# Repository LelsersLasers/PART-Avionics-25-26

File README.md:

# PART Avionics 2025-2026

PART (Purdue Aerial Robotics Team). Work by Comp Avionics and R&D Avionics.

KiCad projects:
- [PDU (power distribution unit)](https://kicanvas.org/?github=https%3A%2F%2Fgithub.com%2FLelsersLasers%2FPART-Avionics-25-26%2Ftree%2Fmain%2FPDB)
- [Pixhawk Carrier](https://kicanvas.org/?github=https%3A%2F%2Fgithub.com%2FLelsersLasers%2FPART-Avionics-25-26%2Ftree%2Fmain%2FKiCad_Main_PCB)

Embedded code:
- PDU

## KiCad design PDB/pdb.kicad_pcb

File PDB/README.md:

# PART Avionics PDB
This is the git repository for the KiCAD schematic & PCB files for the new aircraft's power distribution board.

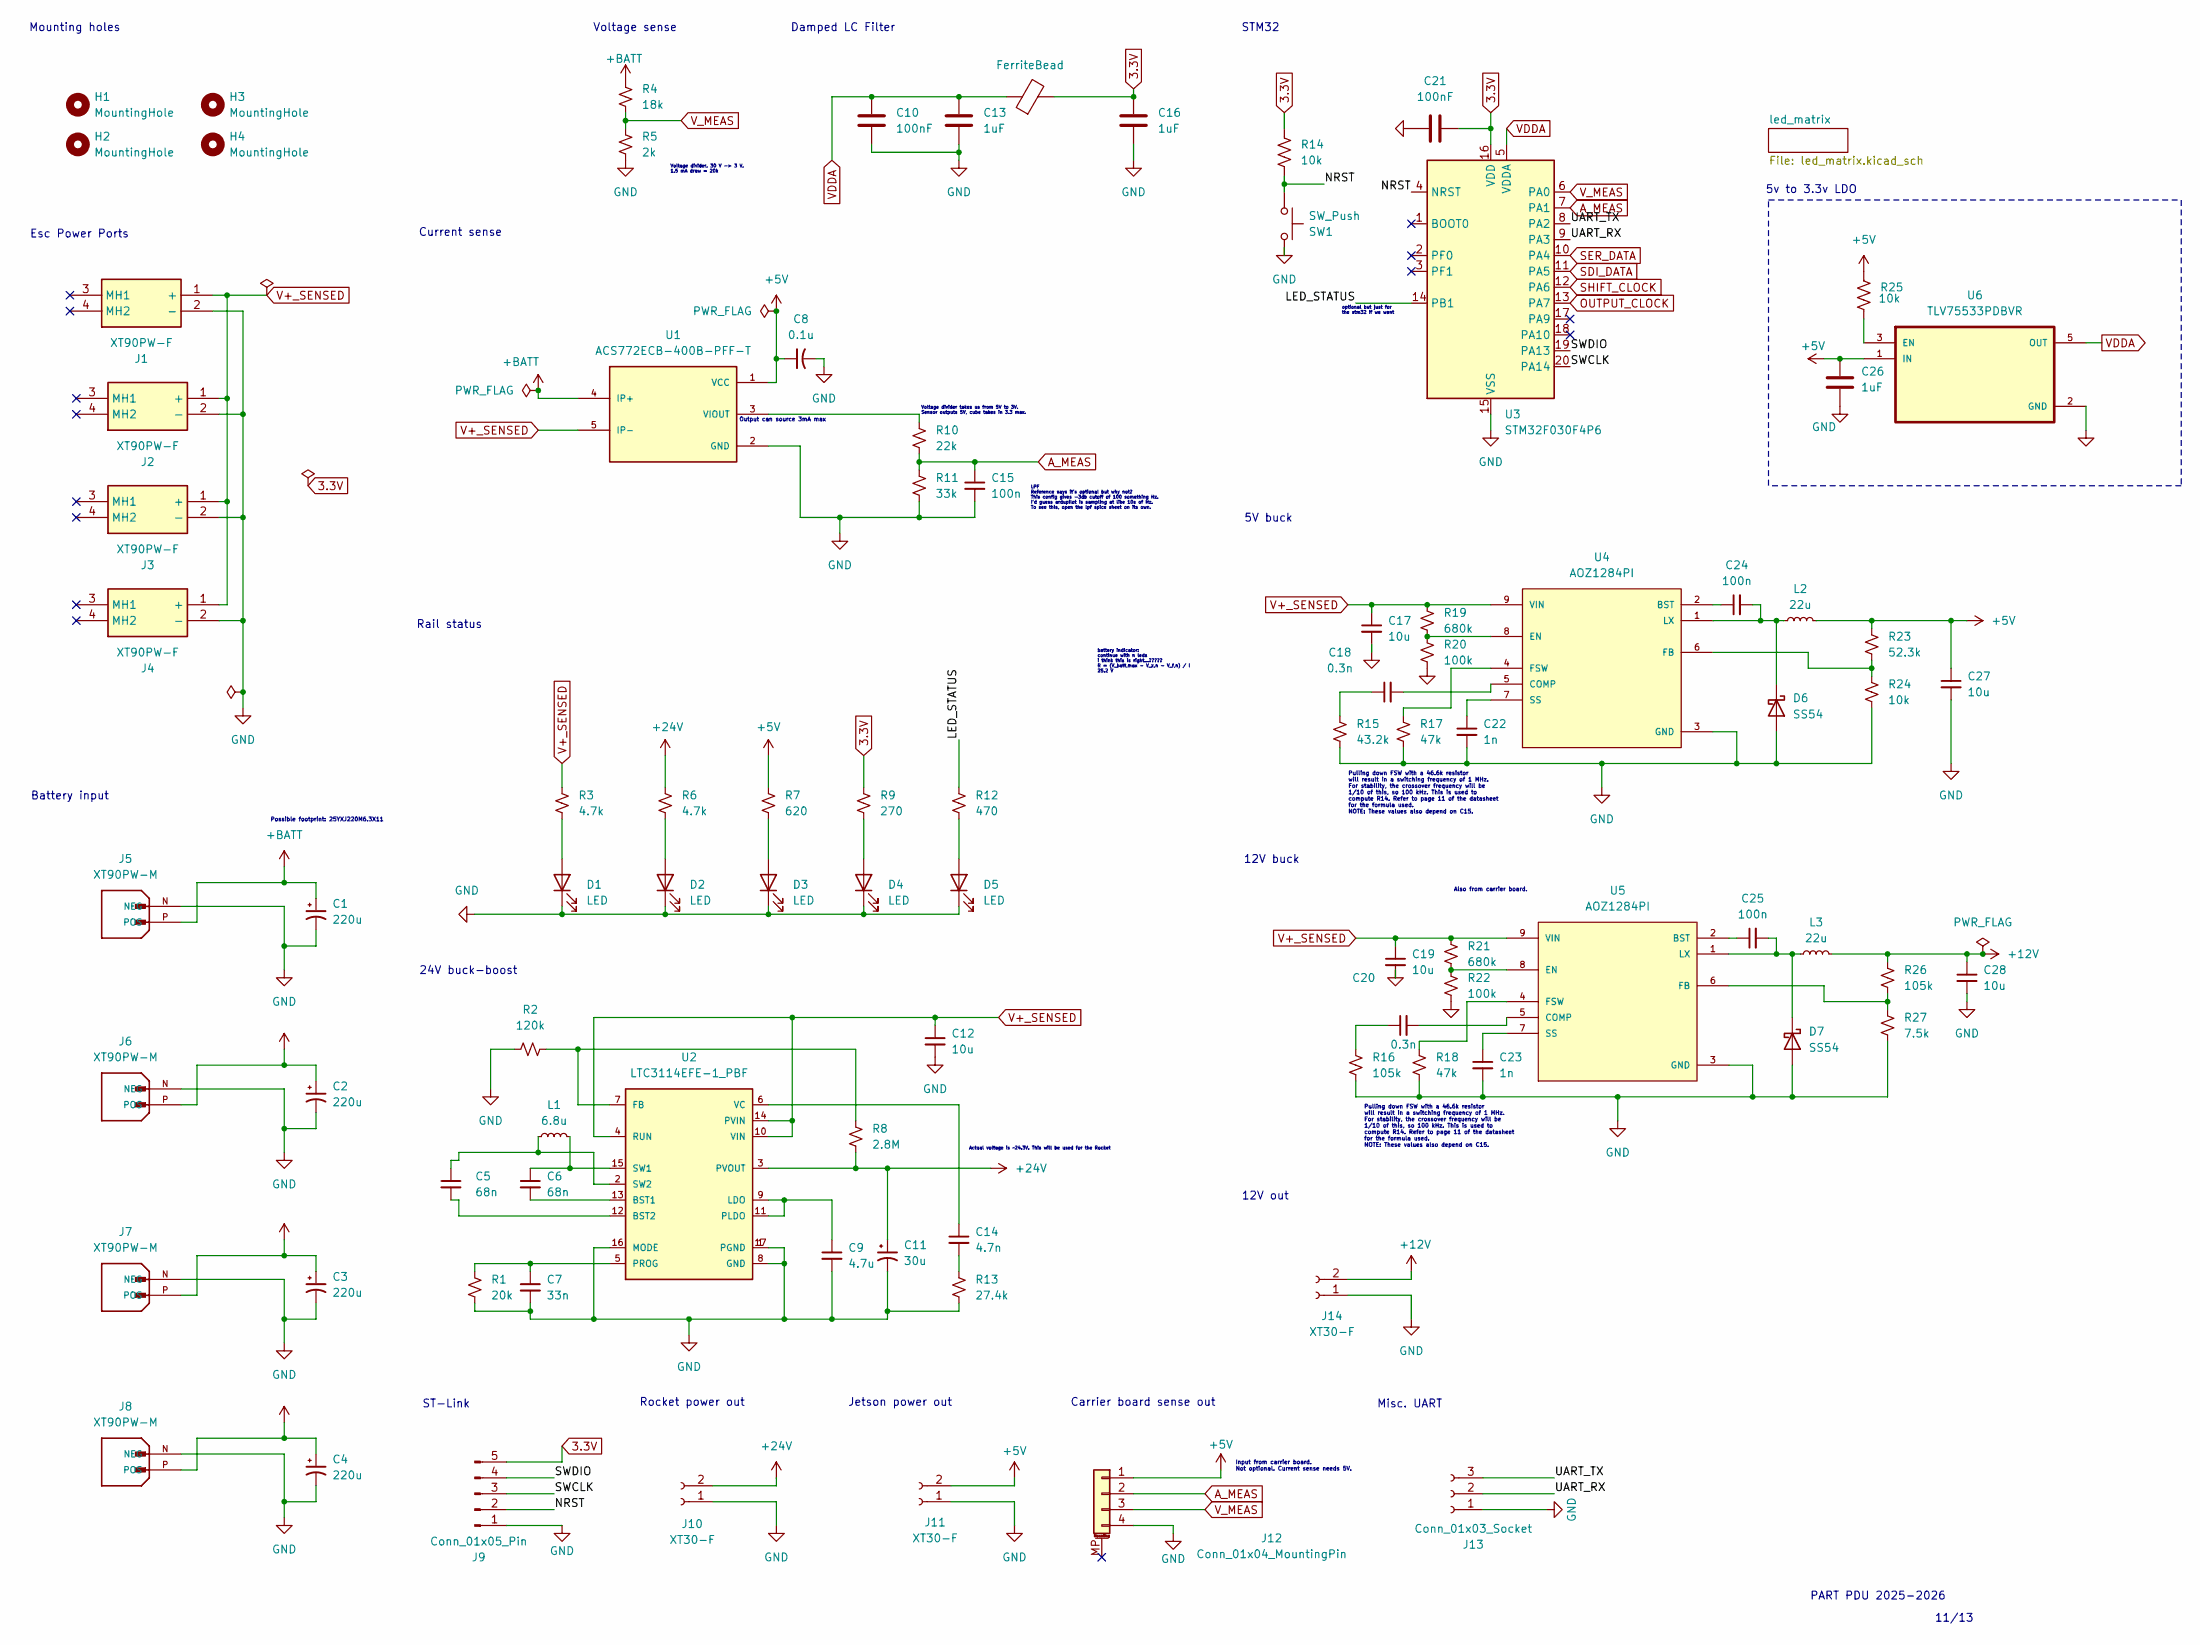
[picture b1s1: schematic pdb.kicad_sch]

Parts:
C1, C2, C3, C4: 220u; CP_Elec_8x10
C5, C6: 68n; C_0603_1608Metric_Pad1.08x0.95mm_HandSolder
C7: 33n; C_0603_1608Metric_Pad1.08x0.95mm_HandSolder
C8: 0.1u; C_0603_1608Metric_Pad1.08x0.95mm_HandSolder
C9: 4.7u; C_0603_1608Metric_Pad1.08x0.95mm_HandSolder
C10, C21: 100nF; C_0603_1608Metric_Pad1.08x0.95mm_HandSolder
C11: 30u; CP_Radial_D5.0mm_P2.00mm
C12, C17, C19, C27, C28: 10u; C_0603_1608Metric_Pad1.08x0.95mm_HandSolder
C13, C16, C26: 1uF; C_0603_1608Metric_Pad1.08x0.95mm_HandSolder
C14: 4.7n; C_0603_1608Metric_Pad1.08x0.95mm_HandSolder
C15, C24, C25: 100n; C_0603_1608Metric_Pad1.08x0.95mm_HandSolder
C18, C20: 0.3n; C_0603_1608Metric_Pad1.08x0.95mm_HandSolder
C22, C23: 1n; C_0603_1608Metric_Pad1.08x0.95mm_HandSolder
D1, D2, D3, D4, D5: LED; LED_0603_1608Metric_Pad1.05x0.95mm_HandSolder
D6, D7: SS54; D_SMA
FB1: FerriteBead; FB_LI0603G121R-10
H1, H2, H3, H4: MountingHole; MountingHole_4mm_Pad
J1, J2, J3, J4: XT90PW-F; XT90PWF; Manufacturer_Part_Number XT90PW-F
J5, J6, J7, J8: XT90PW-M; AMASS_XT90PW-M; PARTREV V00
J9: Conn_01x05_Pin; PinHeader_1x05_P2.54mm_Vertical
J10, J11, J14: XT30-F; AMASS_XT30PW-F
J12: Conn_01x04_MountingPin; JST_GH_SM04B-GHS-TB_1x04-1MP_P1.25mm_Horizontal
J13: Conn_01x03_Socket; PinSocket_1x03_P2.54mm_Vertical
L1: 6.8u; L_0603_1608Metric_Pad1.05x0.95mm_HandSolder
L2, L3: 22u; L_12x12mm_H8mm
R1: 20k; R_0603_1608Metric_Pad0.98x0.95mm_HandSolder
R2: 120k; R_0603_1608Metric_Pad0.98x0.95mm_HandSolder
R3, R6: 4.7k; R_0603_1608Metric_Pad0.98x0.95mm_HandSolder
R4: 18k; R_0603_1608Metric_Pad0.98x0.95mm_HandSolder
R5: 2k; R_0603_1608Metric_Pad0.98x0.95mm_HandSolder
R7: 620; R_0603_1608Metric_Pad0.98x0.95mm_HandSolder
R8: 2.8M; R_0603_1608Metric_Pad0.98x0.95mm_HandSolder
R9: 270; R_0603_1608Metric_Pad0.98x0.95mm_HandSolder
R10: 22k; R_0603_1608Metric_Pad0.98x0.95mm_HandSolder
R11: 33k; R_0603_1608Metric_Pad0.98x0.95mm_HandSolder
R12: 470; R_0603_1608Metric_Pad0.98x0.95mm_HandSolder
R13: 27.4k; R_0603_1608Metric_Pad0.98x0.95mm_HandSolder
R14, R24, R25: 10k; R_0603_1608Metric_Pad0.98x0.95mm_HandSolder
R15: 43.2k; R_0603_1608Metric_Pad0.98x0.95mm_HandSolder
R16, R26: 105k; R_0603_1608Metric_Pad0.98x0.95mm_HandSolder
R17, R18: 47k; R_0603_1608Metric_Pad0.98x0.95mm_HandSolder
R19, R21: 680k; R_0603_1608Metric_Pad0.98x0.95mm_HandSolder
R20, R22: 100k; R_0603_1608Metric_Pad0.98x0.95mm_HandSolder
R23: 52.3k; R_0603_1608Metric_Pad0.98x0.95mm_HandSolder
R27: 7.5k; R_0603_1608Metric_Pad0.98x0.95mm_HandSolder
SW1: SW_Push; SW_SPST_SKQG_WithStem
U1: ACS772ECB-400B-PFF-T; XDCR_ACS772ECB-400B-PFF-T; PARTREV 21
U2: LTC3114EFE-1_PBF; SOP65P640X110-17N
U3: STM32F030F4P6; TSSOP-20_4.4x6.5mm_P0.65mm
U4, U5: AOZ1284PI; SOP127P600X170-9N; PARTREV 0.5
U6: TLV75533PDBVR; SOT95P280X145-5N

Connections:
3.3V: C16.1, C21.2, FB1.2, J9.5, R9.1, R14.1, U3.16 (VDD); also elsewhere on the board
+5V: C8.1, C26.1, C27.1, J11.2, J12.1, L2.2, R7.1, R23.1, R25.1, U1.1 (VCC), U6.1 (IN)
+12V: C28.1, J14.2, L3.2, R26.1
+24V: C11.1, J10.2, R6.1, R8.2, U2.3 (PVOUT)
+BATT: C1.1, C2.1, C3.1, C4.1, J5.P (POS), J6.P (POS), J7.P (POS), J8.P (POS), R4.1, U1.4 (IP+)
/LED_STATUS: R12.1, U3.14 (PB1)
/NRST: J9.2, R14.2, SW1.2, U3.4 (NRST)
/SWCLK: J9.3, U3.20 (PA14)
/SWDIO: J9.4, U3.19 (PA13)
/UART_RX: J13.2, U3.9 (PA3)
/UART_TX: J13.3, U3.8 (PA2)
A_MEAS: C15.1, J12.2, R10.2, R11.1, U3.7 (PA1)
GND: C1.2, C2.2, C3.2, C4.2, C7.2, C8.2, C9.2, C10.2, C11.2, C12.2, C13.2, C15.2, C16.2, C17.2, C19.2, C21.1, C22.2, C23.2, C26.2, C27.2, C28.2, D1.1 (K), D2.1 (K), D3.1 (K), D4.1 (K), D5.1 (K), D6.2 (A), D7.2 (A), J1.2 (-), J2.2 (-), J3.2 (-), J4.2 (-), J5.N (NEG), J6.N (NEG), J7.N (NEG), J8.N (NEG), J9.1, J10.1, J11.1, J12.4, J13.1, J14.1, R1.2, R2.1, R5.2, R11.2, R13.2, R15.2, R16.2, R17.2, R18.2, R20.2, R22.2, R24.2, R27.2, SW1.1, U1.2 (GND), U2.1 (PGND), U2.8 (GND), U2.16 (MODE), U2.17 (PGND), U3.15 (VSS), U4.3 (GND), U5.3 (GND), U6.2 (GND); also elsewhere on the board
unnamed: C14.2, R13.1
unnamed: C18.1, R15.1
unnamed: C20.1, R16.1
unnamed: D1.2 (A), R3.2
unnamed: D2.2 (A), R6.2
unnamed: D3.2 (A), R7.2
unnamed: D4.2 (A), R9.2
unnamed: D5.2 (A), R12.2
unnamed: C24.2, D6.1 (K), L2.1, U4.1 (LX)
unnamed: C25.2, D7.1 (K), L3.1, U5.1 (LX)
unnamed: R10.1, U1.3 (VIOUT)
unnamed: C6.2, U2.13 (BST1)
unnamed: C5.2, U2.12 (BST2)
unnamed: R2.2, R8.1, U2.7 (FB)
unnamed: C9.1, U2.9 (LDO), U2.11 (PLDO)
unnamed: C7.1, R1.1, U2.5 (PROG)
unnamed: C6.1, L1.2, U2.15 (SW1)
unnamed: C5.1, L1.1, U2.2 (SW2)
unnamed: C14.1, U2.6 (VC)
unnamed: C24.1, U4.2 (BST)
unnamed: C18.2, U4.5 (COMP)
unnamed: R19.2, R20.1, U4.8 (EN)
unnamed: R23.2, R24.1, U4.6 (FB)
unnamed: R17.1, U4.4 (FSW)
unnamed: C22.1, U4.7 (SS)
unnamed: C25.1, U5.2 (BST)
unnamed: C20.2, U5.5 (COMP)
unnamed: R21.2, R22.1, U5.8 (EN)
unnamed: R26.2, R27.1, U5.6 (FB)
unnamed: R18.1, U5.4 (FSW)
unnamed: C23.1, U5.7 (SS)
unnamed: R25.2, U6.3 (EN)
OUTPUT_CLOCK: U3.13 (PA7); also elsewhere on the board
SDI_DATA: U3.11 (PA5); also elsewhere on the board
SER_DATA: U3.10 (PA4); also elsewhere on the board
SHIFT_CLOCK: U3.12 (PA6); also elsewhere on the board
V+_SENSED: C12.1, C17.1, C19.1, J1.1 (+), J2.1 (+), J3.1 (+), J4.1 (+), R3.1, R19.1, R21.1, U1.5 (IP-), U2.4 (RUN), U2.10 (VIN), U2.14 (PVIN), U4.9 (VIN), U5.9 (VIN)
VDDA: C10.1, C13.1, FB1.1, U3.5 (VDDA), U6.5 (OUT)
V_MEAS: J12.3, R4.2, R5.1, U3.6 (PA0)

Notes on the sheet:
11/13
Rocket power out
battery indicator: continue with n leds i think this is right...????? R = (V_batt,max - V_z,n - V_f,n) / I 25.2 V
optional but just for the stm32 if we want
Mounting holes
24V buck-boost
Voltage divider. 30 V -> 3 V. 1.5 mA draw = 20k
12V out
Also from carrier board.
Misc. UART
STM32
Voltage sense
Esc Power Ports
LPF Reference says it's optional but why not? This config gives -3db cutoff of 100 something Hz. I'd guess ardupilot is sampling at like 10s of Hz. To see this, open the lpf spice sheet on its own.
Output can source 3mA max
5V buck
Current sense
Voltage divider takes us from 5V to 3V. Sensor outputs 5V, cube takes in 3.3 max.
Jetson power out
Input from carrier board. Not optional. Current sense needs 5V.
Damped LC Filter
Rail status
Actual voltage is ~24.3V. This will be used for the Rocket
Carrier board sense out
12V buck
ST-Link
Battery input
5v to 3.3v LDO
PART PDU 2025-2026
Possible footprint: 25YXJ220M6.3X11
Pulling down FSW with a 46.6k resistor will result in a switching frequency of 1 MHz. For stability, the crossover frequency will be 1/10 of this, so 100 kHz. This is used to compute R14. Refer to page 11 of the datasheet for the formula used. NOTE: These values also depend on C15.

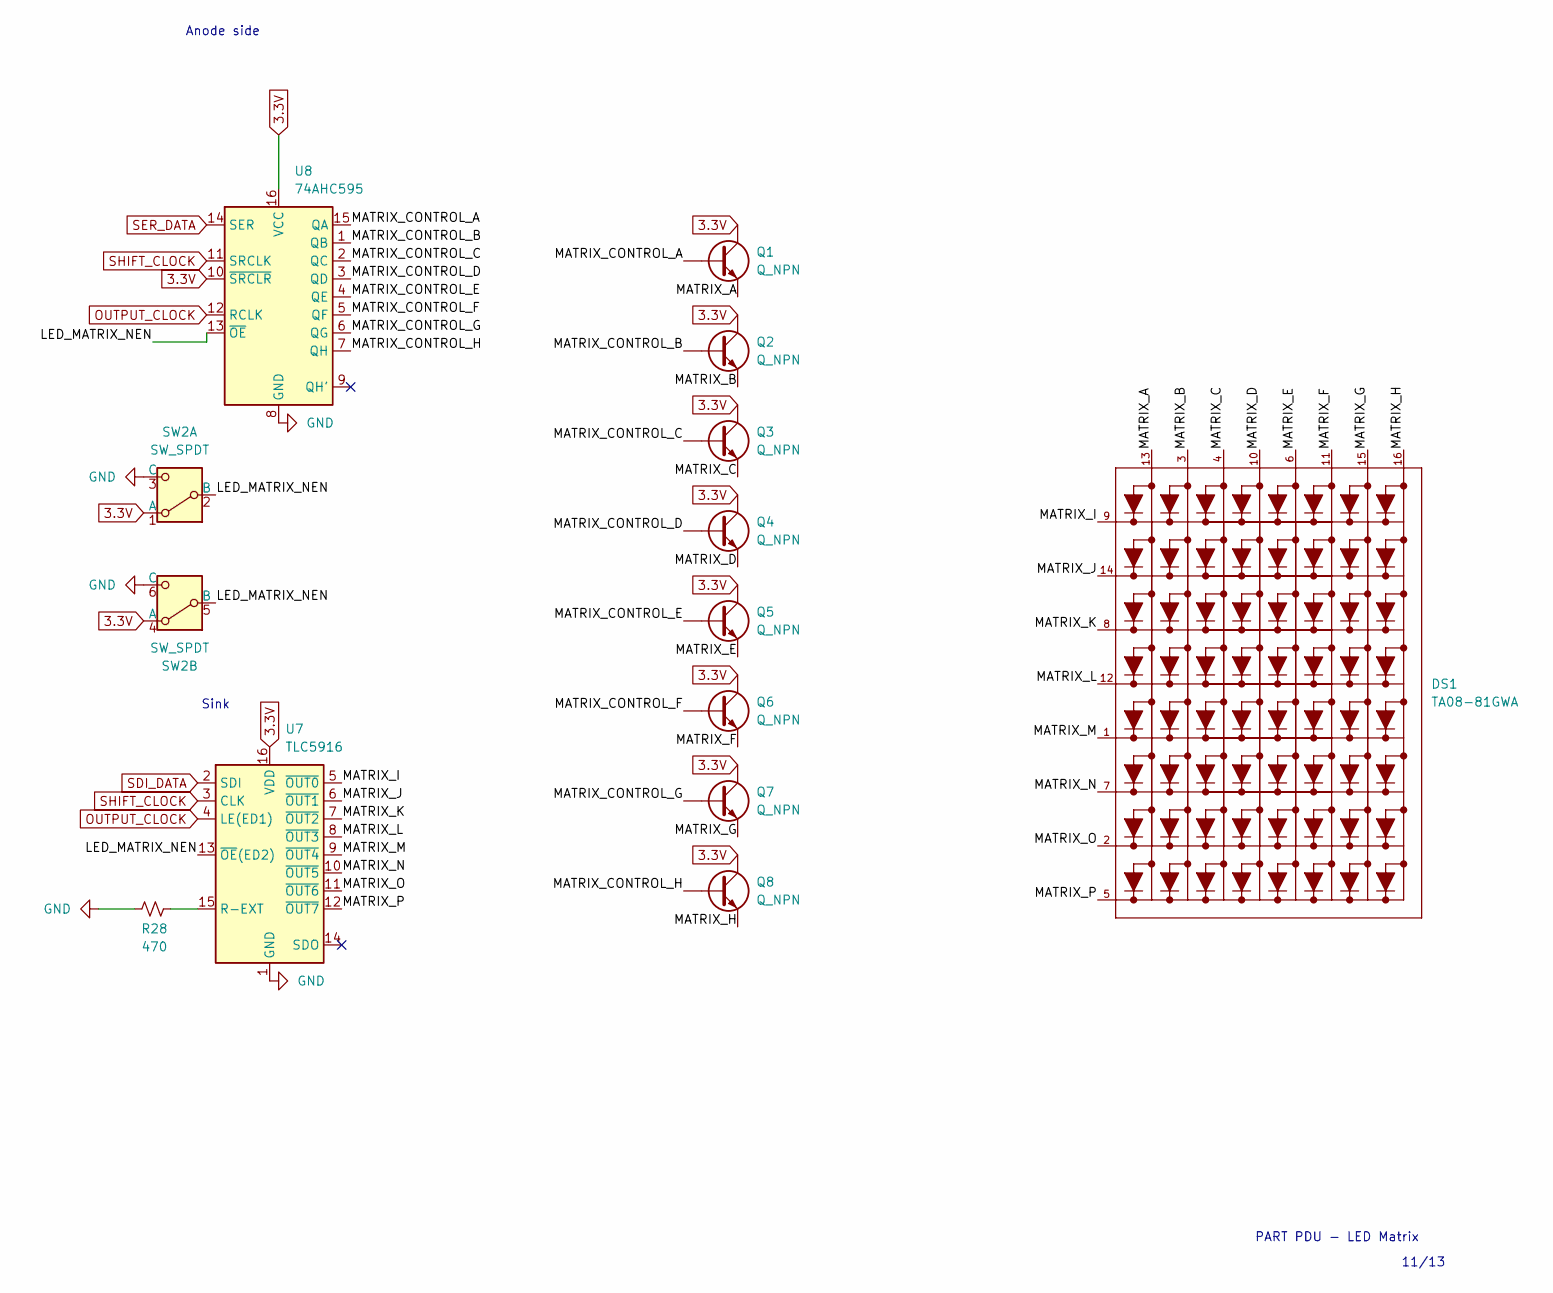
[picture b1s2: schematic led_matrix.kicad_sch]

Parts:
DS1: TA08-81GWA; DISPLAY_TA08-81GWA; PARTREV V.11A
Q1, Q2, Q3, Q4, Q5, Q6, Q7, Q8: Q_NPN; TSOT-23-Fixed
R28: 470; R_0603_1608Metric_Pad0.98x0.95mm_HandSolder
SW2: SW_SPDT; JS202011SCQN
U7: TLC5916; DIP-16_W7.62mm
U8: 74AHC595; DIP-16_W7.62mm

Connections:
3.3V: Q1.C, Q2.C, Q3.C, Q4.C, Q5.C, Q6.C, Q7.C, Q8.C, SW2.1 (A), SW2.4 (A), U7.16 (VDD), U8.10 (~SRCLR), U8.16 (VCC); also elsewhere on the board
/led_matrix/LED_MATRIX_NEN: SW2.2 (B), SW2.5 (B), U7.13 (~OE(ED2)), U8.13 (~OE)
/led_matrix/MATRIX_A: DS1.13, Q1.E
/led_matrix/MATRIX_B: DS1.3, Q2.E
/led_matrix/MATRIX_C: DS1.4, Q3.E
/led_matrix/MATRIX_CONTROL_A: Q1.B, U8.15 (QA)
/led_matrix/MATRIX_CONTROL_B: Q2.B, U8.1 (QB)
/led_matrix/MATRIX_CONTROL_C: Q3.B, U8.2 (QC)
/led_matrix/MATRIX_CONTROL_D: Q4.B, U8.3 (QD)
/led_matrix/MATRIX_CONTROL_E: Q5.B, U8.4 (QE)
/led_matrix/MATRIX_CONTROL_F: Q6.B, U8.5 (QF)
/led_matrix/MATRIX_CONTROL_G: Q7.B, U8.6 (QG)
/led_matrix/MATRIX_CONTROL_H: Q8.B, U8.7 (QH)
/led_matrix/MATRIX_D: DS1.10, Q4.E
/led_matrix/MATRIX_E: DS1.6, Q5.E
/led_matrix/MATRIX_F: DS1.11, Q6.E
/led_matrix/MATRIX_G: DS1.15, Q7.E
/led_matrix/MATRIX_H: DS1.16, Q8.E
/led_matrix/MATRIX_I: DS1.9, U7.5 (~OUT0)
/led_matrix/MATRIX_J: DS1.14, U7.6 (~OUT1)
/led_matrix/MATRIX_K: DS1.8, U7.7 (~OUT2)
/led_matrix/MATRIX_L: DS1.12, U7.8 (~OUT3)
/led_matrix/MATRIX_M: DS1.1, U7.9 (~OUT4)
/led_matrix/MATRIX_N: DS1.7, U7.10 (~OUT5)
/led_matrix/MATRIX_O: DS1.2, U7.11 (~OUT6)
/led_matrix/MATRIX_P: DS1.5, U7.12 (~OUT7)
GND: R28.1, SW2.3 (C), SW2.6 (C), U7.1 (GND), U8.8 (GND); also elsewhere on the board
unnamed: R28.2, U7.15 (R-EXT)
OUTPUT_CLOCK: U7.4 (LE(ED1)), U8.12 (RCLK); also elsewhere on the board
SDI_DATA: U7.2 (SDI); also elsewhere on the board
SER_DATA: U8.14 (SER); also elsewhere on the board
SHIFT_CLOCK: U7.3 (CLK), U8.11 (SRCLK); also elsewhere on the board

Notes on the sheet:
11/13
PART PDU - LED Matrix
Sink
Anode side

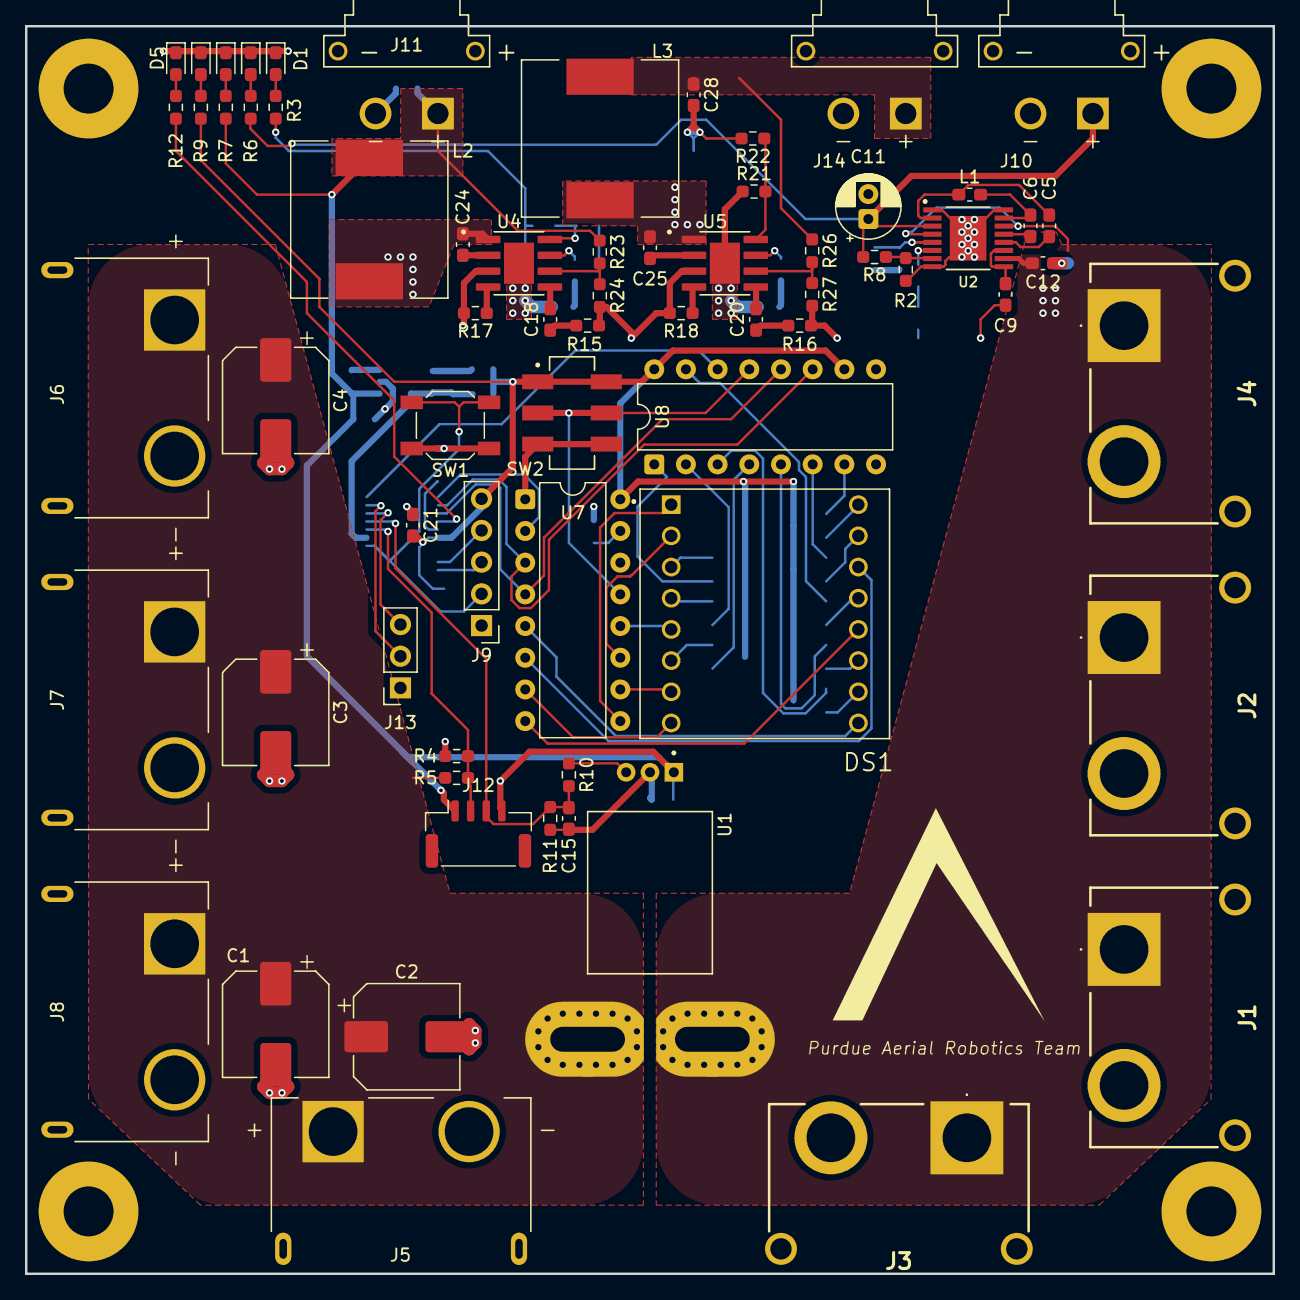
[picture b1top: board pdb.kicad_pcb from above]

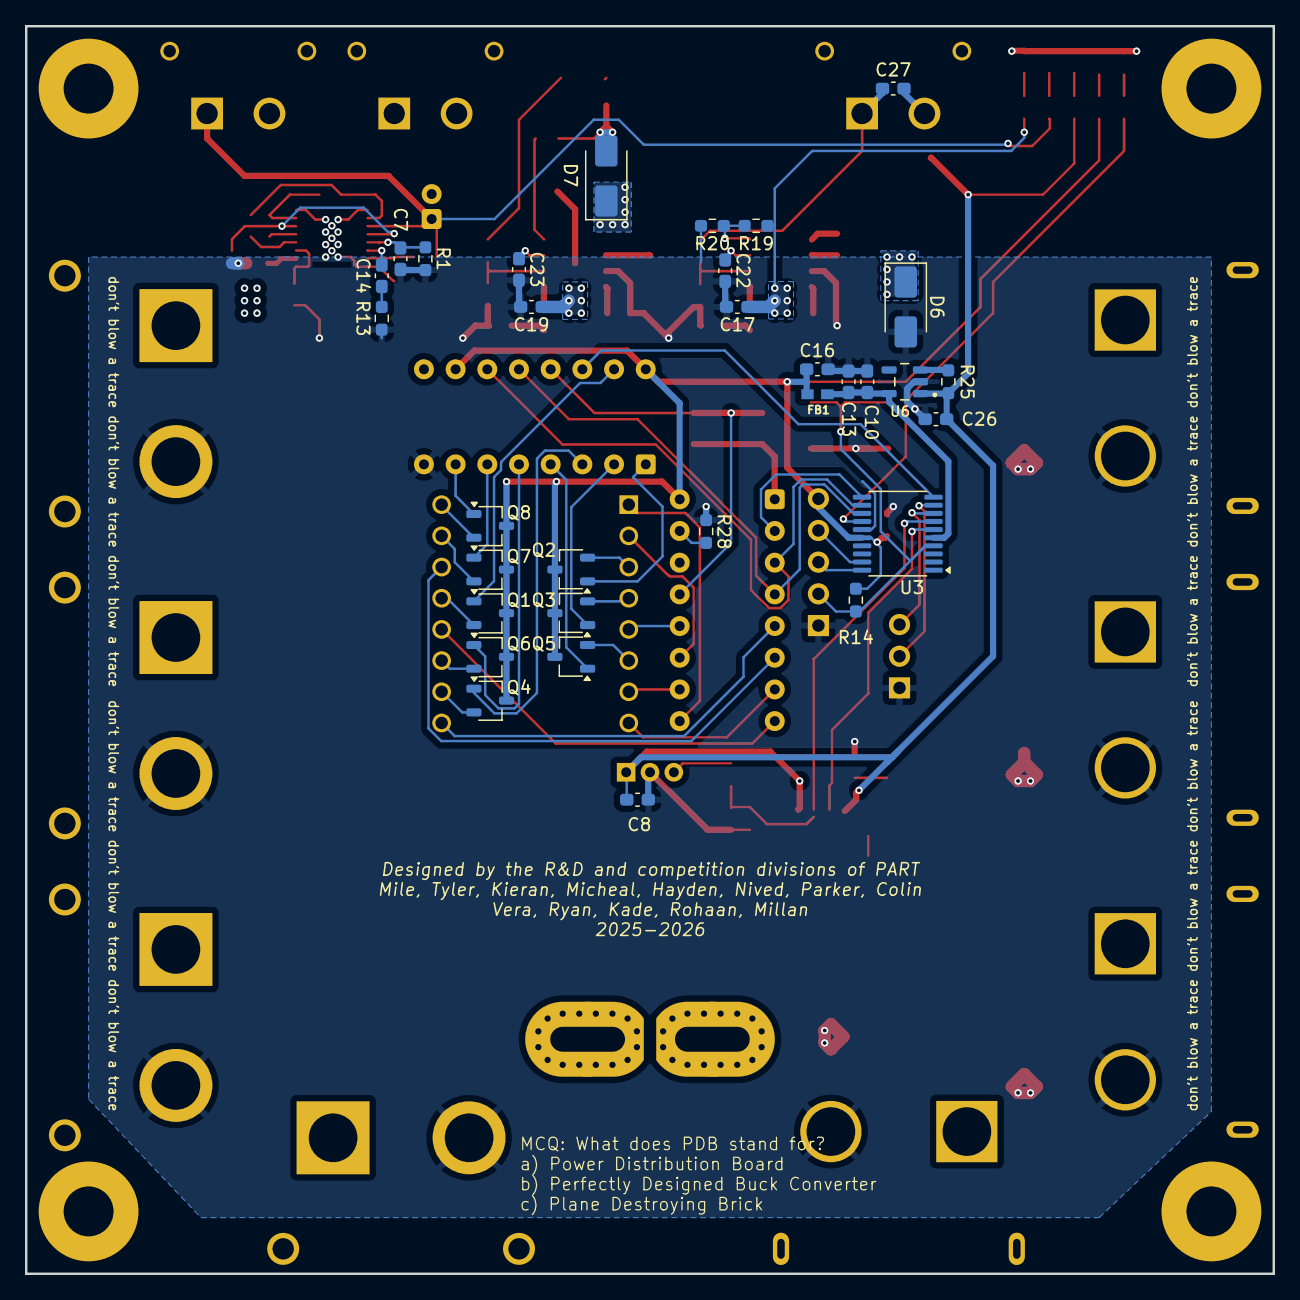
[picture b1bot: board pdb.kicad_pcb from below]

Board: 4 copper layers, 100.0 x 100.0 mm, 104 parts (32 on the bottom side), 78 nets.

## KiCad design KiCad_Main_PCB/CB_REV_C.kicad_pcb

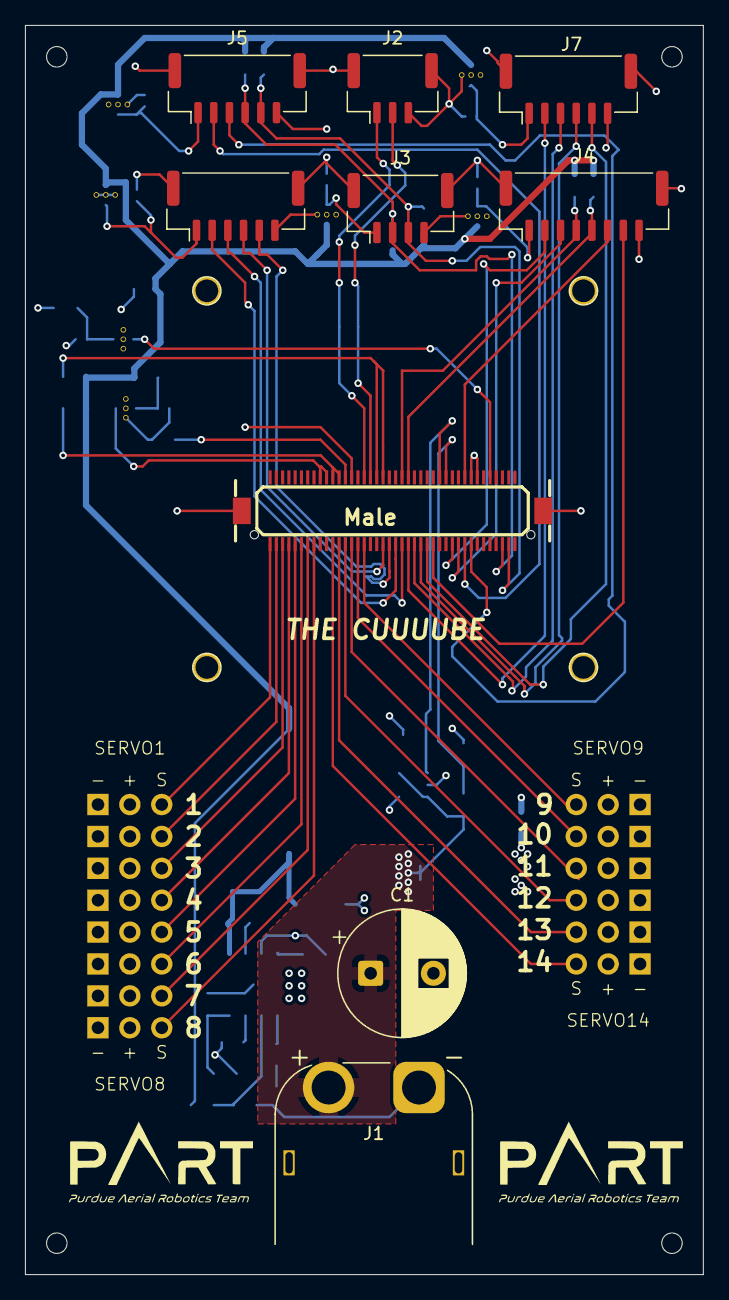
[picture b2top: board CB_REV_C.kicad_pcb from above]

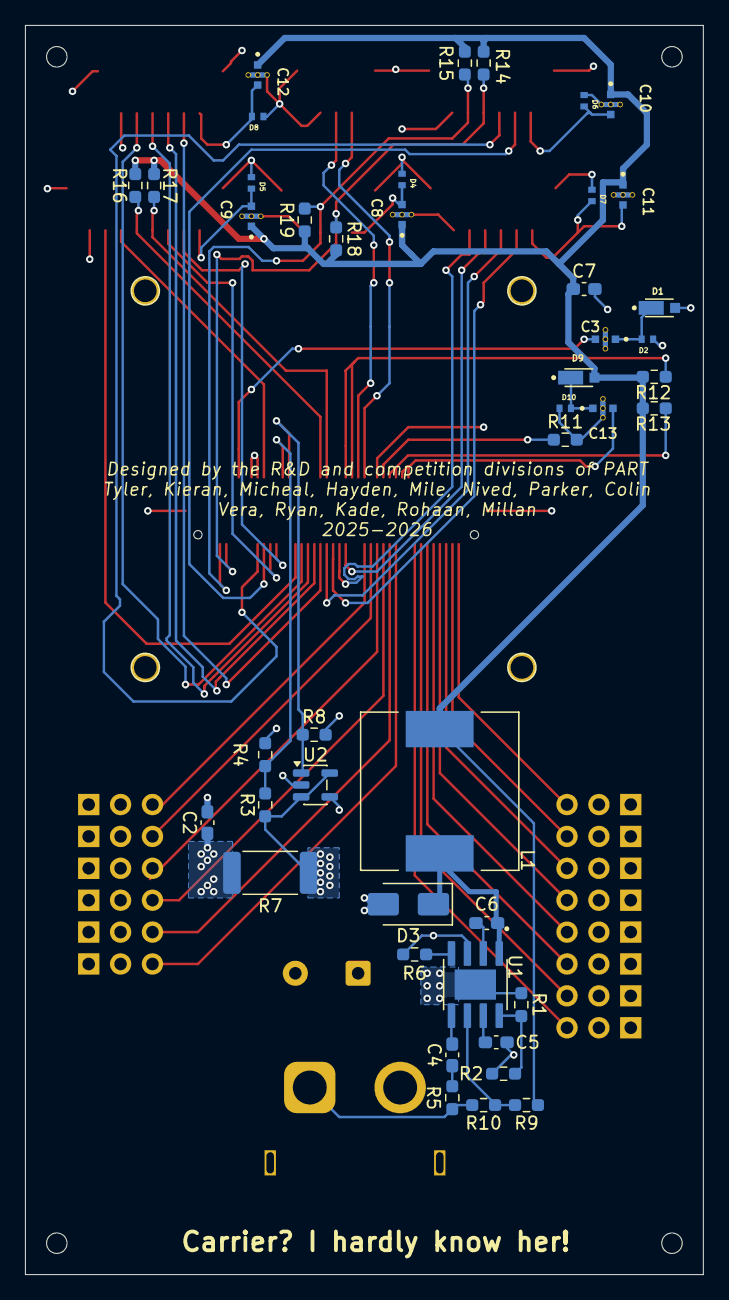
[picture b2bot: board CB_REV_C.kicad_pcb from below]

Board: 4 copper layers, 54.0 x 99.5 mm, 67 parts (44 on the bottom side), 60 nets.

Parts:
C1: 470u; CP_Radial_D10.0mm_P5.00mm
C2, C7: 10u; C_0603_1608Metric_Pad1.08x0.95mm_HandSolder
C3, C8, C9, C10, C11, C12, C13: NFM18PC104R1C3D; FIL_NFM18PC104R1C3D
C4: 3n; C_0603_1608Metric_Pad1.08x0.95mm_HandSolder
C5, C6: 0.1u; C_0603_1608Metric_Pad1.08x0.95mm_HandSolder
D1, D9: MSS1P4-M3; MSS1P4-M3_89A
D2, D4, D5, D6, D7, D8, D10: PESD0402-140
D3: SS54; D_SMA
J1: XT60; AMASS_XT60PW-M_1x02_P7.20mm_Horizontal
J2: Conn_01x03; JST_GH_BM03B-GHS-TBT_1x03-1MP_P1.25mm_Vertical
J3: Conn_01x04_MountingPin; JST_GH_BM04B-GHS-TBT_1x04-1MP_P1.25mm_Vertical
J4: Conn_01x08_MountingPin; JST_GH_BM08B-GHS-TBT_1x08-1MP_P1.25mm_Vertical
J5, J6, J7: Conn_01x06_MountingPin; JST_GH_BM06B-GHS-TBT_1x06-1MP_P1.25mm_Vertical
J8, J9, J10, J11, J12, J13, J14, J15, J16, J17, J18, J19, J20, J21: Conn_01x03_Pin; Packable_PinHeader_1x03_P2.54mm_Vertical
J22: Cube80Pin; CON-DF17-80M
L1: 22u; L_12x12mm_H8mm
R1, R2: 47k; R_0603_1608Metric_Pad0.98x0.95mm_HandSolder
R3: 47K; R_0603_1608Metric_Pad0.98x0.95mm_HandSolder
R4: 82K; R_0603_1608Metric_Pad0.98x0.95mm_HandSolder
R5: 43.7k; R_0603_1608Metric_Pad0.98x0.95mm_HandSolder
R6: 46.4k; R_0603_1608Metric_Pad0.98x0.95mm_HandSolder
R7: 0.01; R_2512_6332Metric_Pad1.40x3.35mm_HandSolder
R8: 75k; R_0603_1608Metric_Pad0.98x0.95mm_HandSolder
R9: 52.3k; R_0603_1608Metric_Pad0.98x0.95mm_HandSolder
R10, R14, R15, R16, R17, R18, R19: 10k; R_0603_1608Metric_Pad0.98x0.95mm_HandSolder
R11, R12, R13: 100k; R_0603_1608Metric_Pad0.98x0.95mm_HandSolder
U1: AOZ1284PI; SOP127P600X170-9N
U2: INA138; SOT-23-5

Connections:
+5V_PERIPH: C7.1, C8.1, C9.1, C10.1, C11.1, C12.1, D9.2 (A), L1.2, R9.1, R12.1, R13.1, R14.2, R15.1, R16.2, R17.1, R18.2, R19.1
+BATT: C2.1, D1.2 (A), J8.2, J9.2, J10.2, J11.2, J12.2, J13.2, J14.2, J15.2, J16.2, J17.2, J18.2, J19.2, J20.2, J21.2, J22.53, R1.1, R7.2, U1.9 (VIN), U2.4 (-)
/80_Pin/FMU_CH1_PROT: J16.3, J22.50
/80_Pin/FMU_CH2_PROT: J17.3, J22.52
/80_Pin/FMU_CH3_PROT: J18.3, J22.54
/80_Pin/FMU_CH4_PROT: J19.3, J22.56
/80_Pin/FMU_CH5_PROT: J20.3, J22.58
/80_Pin/FMU_CH6_PROT: J21.3, J22.60
/80_Pin/IO_CH1_PROT: J8.3, J22.80
/80_Pin/IO_CH2_PROT: J9.3, J22.78
/80_Pin/IO_CH3_PROT: J10.3, J22.76
/80_Pin/IO_CH4_PROT: J11.3, J22.74
/80_Pin/IO_CH5_PROT: J12.3, J22.72
/80_Pin/IO_CH6_PROT: J13.3, J22.70
/80_Pin/IO_CH7_PROT: J14.3, J22.68
/80_Pin/IO_CH8_PROT: J15.3, J22.66
/80_Pin/VBUS_VALID: J22.57, J22.59, R13.2
/80_Pin/VDD_5V_HIPOWER_OC: J22.43, J22.45, R12.2
/80_Pin/VDD_5V_IN_PROT: C13.3, J22.61, J22.63
/80_Pin/VDD_BRICK_VALID: J22.55, R11.1
/BATT_MOT_A_MEAS: J2.1, J22.49
/BATT_MOT_V_MEAS: J2.2, J22.47
/BATT_SERVO_A_MEAS: J22.25, R8.1, U2.1
/BATT_SERVO_V_MEAS: J22.23, R3.2, R4.2
/I2C_1_SCL: J4.4, J22.37, R16.1
/I2C_1_SDA: J4.5, J22.35, R17.2
/I2C_2_SCL: J3.2, J5.4, J22.6, R14.1, R18.1
/I2C_2_SDA: J3.3, J5.5, J22.4, R15.2, R19.2
/SAFETY: J4.6, J22.17
/SERIAL1_CTS: J6.4, J22.44
/SERIAL1_RTS: J6.5, J22.42
/SERIAL1_RX: J6.3, J22.38
/SERIAL1_TX: J6.2, J22.40
/SERIAL2_CTS: J7.4, J22.32
/SERIAL2_RTS: J7.5, J22.30
/SERIAL2_RX: J7.3, J22.34
/SERIAL2_TX: J7.2, J22.36
/SERIAL3_RX: J4.3, J22.20
/SERIAL3_TX: J4.2, J22.22
/SERIAL4_RX: J5.3, J22.16
/SERIAL4_TX: J5.2, J22.18
/VDD_SERVO_IN: C3.3, J22.9
/~IO-LED_SAFET_PROT: J4.7, J22.28
GND: C1.2, C2.2, C3.2, C5.2, C7.2, C8.2, C9.2, C10.2, C11.2, C12.2, C13.2, D2.1 (A1), D3.2 (A), D4.1 (A1), D5.1 (A1), D6.1 (A1), D7.1 (A1), D8.1 (A1), D10.1 (A1), J1.1 (-), J2.3, J2.MP (MountPin), J3.4, J3.MP (MountPin), J4.8, J4.MP (MountPin), J5.6, J5.MP (MountPin), J6.6, J6.MP (MountPin), J7.6, J7.MP (MountPin), J8.1, J9.1, J10.1, J11.1, J12.1, J13.1, J14.1, J15.1, J16.1, J17.1, J18.1, J19.1, J20.1, J21.1, J22.13, J22.15, J22.GND, R2.2, R4.1, R5.2, R6.2, R8.2, R10.2, R11.2, U1.3 (GND), U2.2 (GND)
unnamed: C4.1, R5.1
unnamed: C3.1, D1.1 (K), D2.2 (A2)
unnamed: C6.2, D3.1 (K), L1.1, U1.1 (LX)
unnamed: C8.3, D4.2 (A2), J3.1
unnamed: C9.3, D5.2 (A2), J4.1
unnamed: C10.3, D6.2 (A2), J5.1
unnamed: C11.3, D7.2 (A2), J6.1
unnamed: C12.3, D8.2 (A2), J7.1
unnamed: C13.1, D9.1 (K), D10.2 (A2)
unnamed: C1.1, J1.2 (+), R3.1, R7.1, U2.3 (+), U2.5 (V+)
unnamed: C6.1, U1.2 (BST)
unnamed: C4.2, U1.5 (COMP)
unnamed: R1.2, R2.1, U1.8 (EN)
unnamed: R9.2, R10.1, U1.6 (FB)
unnamed: R6.1, U1.4 (FSW)
unnamed: C5.1, U1.7 (SS)

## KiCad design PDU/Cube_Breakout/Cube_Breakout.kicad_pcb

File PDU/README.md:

# Lunabotics-Battery-Protection-Circuit
Battery Protection Circuit based around 555 timer for Purdue Lunabotics 2025-2026

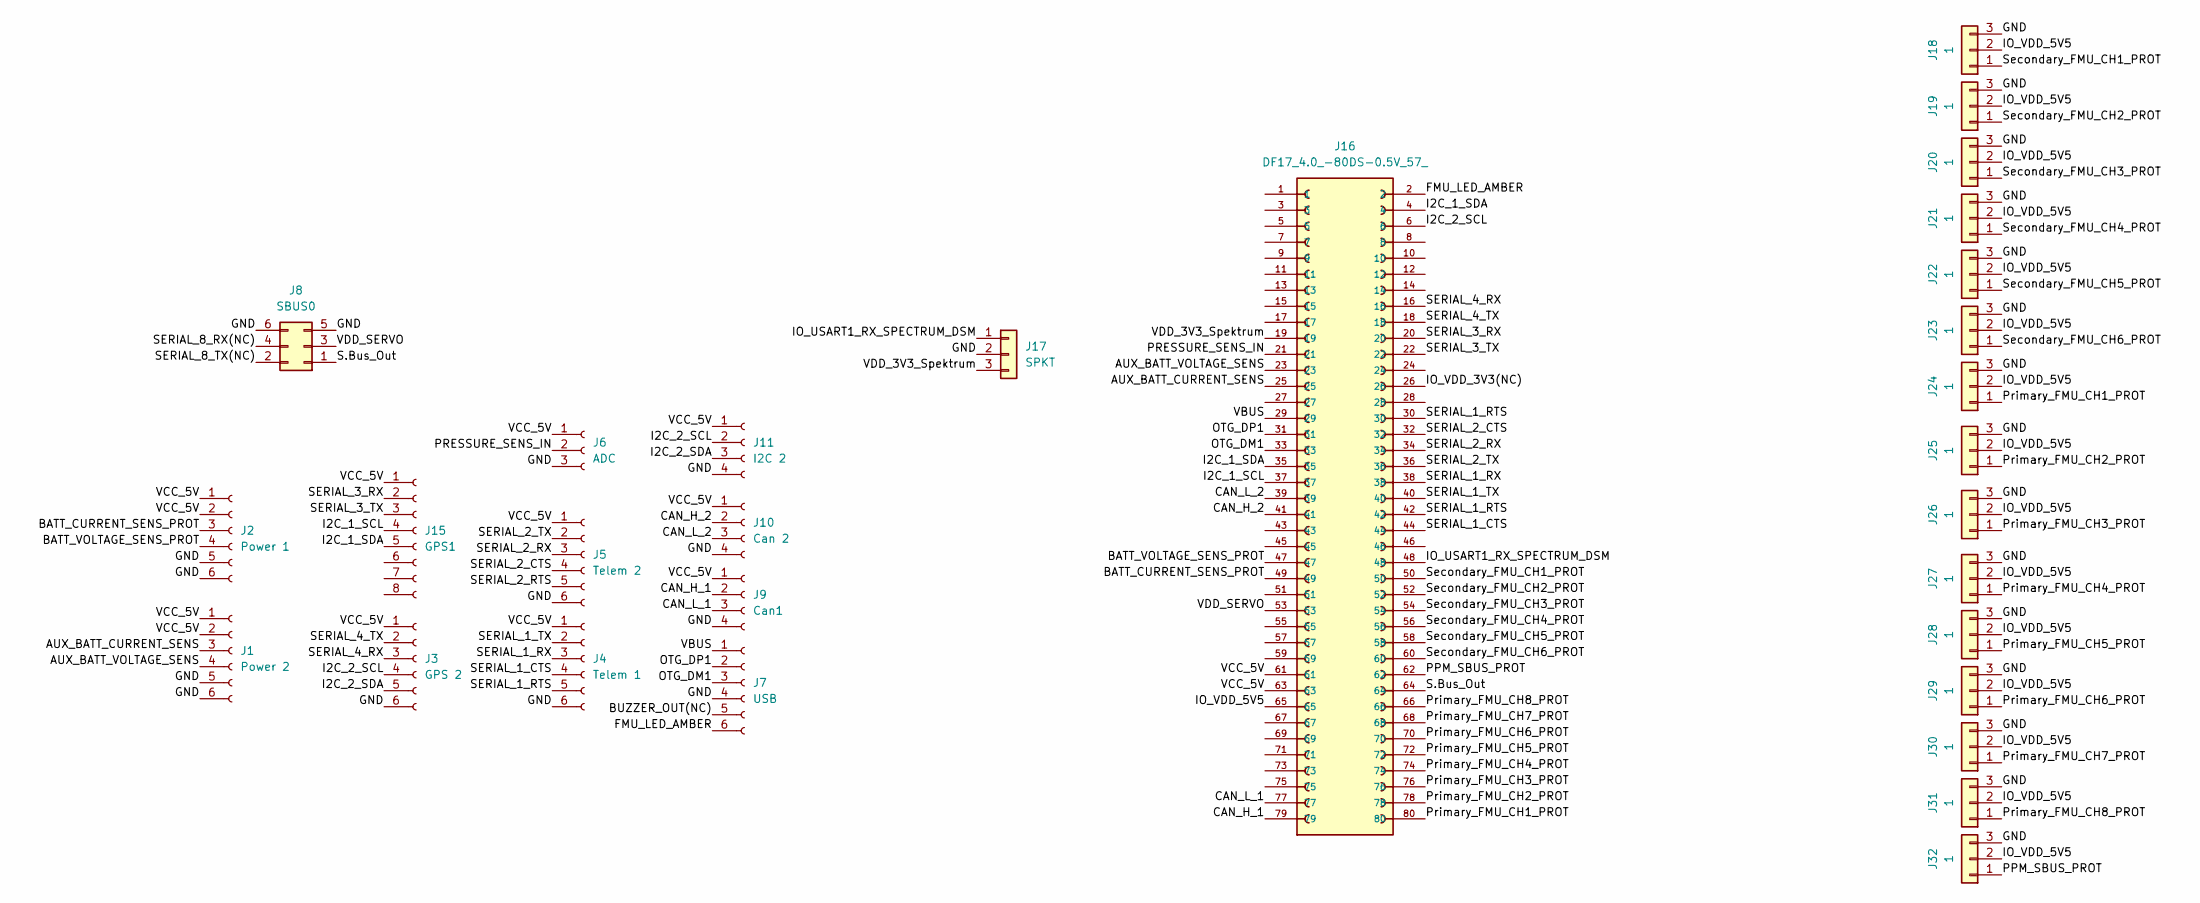
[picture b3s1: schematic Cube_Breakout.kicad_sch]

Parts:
J1: Power 2; Molex_CLIK-Mate_502443-0670_1x06-1MP_P2.00mm_Vertical
J2: Power 1; Molex_CLIK-Mate_502443-0670_1x06-1MP_P2.00mm_Vertical
J3: GPS 2; JST_GH_BM06B-GHS-TBT_1x06-1MP_P1.25mm_Vertical
J4: Telem 1; JST_GH_BM06B-GHS-TBT_1x06-1MP_P1.25mm_Vertical
J5: Telem 2; JST_GH_BM06B-GHS-TBT_1x06-1MP_P1.25mm_Vertical
J6: ADC; JST_GH_BM03B-GHS-TBT_1x03-1MP_P1.25mm_Vertical
J7: USB; JST_GH_BM06B-GHS-TBT_1x06-1MP_P1.25mm_Vertical
J8: SBUS0; PinHeader_2x03_P2.54mm_Vertical
J9: Can1; JST_GH_BM04B-GHS-TBT_1x04-1MP_P1.25mm_Vertical
J10: Can 2; JST_GH_BM04B-GHS-TBT_1x04-1MP_P1.25mm_Vertical
J11: I2C 2; JST_GH_BM04B-GHS-TBT_1x04-1MP_P1.25mm_Vertical
J15: GPS1; JST_GH_BM08B-GHS-TBT_1x08-1MP_P1.25mm_Vertical
J16: DF17_4.0_-80DS-0.5V_57_; HRS_DF17_4.0_-80DS-0.5V_57_
J17: SPKT; PinHeader_1x03_P2.54mm_Vertical
J18, J19, J20, J21, J22, J23, J24, J25, J26, J27, J28, J29, J30, J31, J32: 1; PinHeader_1x03_P2.54mm_Vertical

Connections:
/AUX_BATT_CURRENT_SENS: J1.3, J16.25
/AUX_BATT_VOLTAGE_SENS: J1.4, J16.23
/BATT_CURRENT_SENS_PROT: J2.3, J16.49
/BATT_VOLTAGE_SENS_PROT: J2.4, J16.47
/BUZZER_OUT(NC): J7.5
/CAN_H_1: J9.2, J16.79
/CAN_H_2: J10.2, J16.41
/CAN_L_1: J9.3, J16.77
/CAN_L_2: J10.3, J16.39
/FMU_LED_AMBER: J7.6, J16.2
/GND: J1.5, J1.6, J2.5, J2.6, J3.6, J4.6, J5.6, J6.3, J7.4, J8.5, J8.6, J9.4, J10.4, J11.4, J17.2, J18.3, J19.3, J20.3, J21.3, J22.3, J23.3, J24.3, J25.3, J26.3, J27.3, J28.3, J29.3, J30.3, J31.3, J32.3
/I2C_1_SCL: J15.4, J16.37
/I2C_1_SDA: J15.5, J16.4, J16.35
/I2C_2_SCL: J3.4, J11.2, J16.6
/I2C_2_SDA: J3.5, J11.3
/IO_USART1_RX_SPECTRUM_DSM: J16.48, J17.1
/IO_VDD_3V3(NC): J16.26
/IO_VDD_5V5: J16.65, J18.2, J19.2, J20.2, J21.2, J22.2, J23.2, J24.2, J25.2, J26.2, J27.2, J28.2, J29.2, J30.2, J31.2, J32.2
/OTG_DM1: J7.3, J16.33
/OTG_DP1: J7.2, J16.31
/PPM_SBUS_PROT: J16.62, J32.1
/PRESSURE_SENS_IN: J6.2, J16.21
/Primary_FMU_CH1_PROT: J16.80, J24.1
/Primary_FMU_CH2_PROT: J16.78, J25.1
/Primary_FMU_CH3_PROT: J16.76, J26.1
/Primary_FMU_CH4_PROT: J16.74, J27.1
/Primary_FMU_CH5_PROT: J16.72, J28.1
/Primary_FMU_CH6_PROT: J16.70, J29.1
/Primary_FMU_CH7_PROT: J16.68, J30.1
/Primary_FMU_CH8_PROT: J16.66, J31.1
/S.Bus_Out: J8.1, J16.64
/SERIAL_1_CTS: J4.4, J16.44
/SERIAL_1_RTS: J4.5, J16.30, J16.42
/SERIAL_1_RX: J4.3, J16.38
/SERIAL_1_TX: J4.2, J16.40
/SERIAL_2_CTS: J5.4, J16.32
/SERIAL_2_RTS: J5.5
/SERIAL_2_RX: J5.3, J16.34
/SERIAL_2_TX: J5.2, J16.36
/SERIAL_3_RX: J15.2, J16.20
/SERIAL_3_TX: J15.3, J16.22
/SERIAL_4_RX: J3.3, J16.16
/SERIAL_4_TX: J3.2, J16.18
/SERIAL_8_RX(NC): J8.4
/SERIAL_8_TX(NC): J8.2
/Secondary_FMU_CH1_PROT: J16.50, J18.1
/Secondary_FMU_CH2_PROT: J16.52, J19.1
/Secondary_FMU_CH3_PROT: J16.54, J20.1
/Secondary_FMU_CH4_PROT: J16.56, J21.1
/Secondary_FMU_CH5_PROT: J16.58, J22.1
/Secondary_FMU_CH6_PROT: J16.60, J23.1
/VBUS: J7.1, J16.29
/VCC_5V: J1.1, J1.2, J2.1, J2.2, J3.1, J4.1, J5.1, J6.1, J9.1, J10.1, J11.1, J15.1, J16.61, J16.63
/VDD_3V3_Spektrum: J16.19, J17.3
/VDD_SERVO: J8.3, J16.53

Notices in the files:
PART-PDB-STM32/Core/Src/main.c:
Copyright (c) 2026 STMicroelectronics.
All rights reserved.
This software is licensed under terms that can be found in the LICENSE file
